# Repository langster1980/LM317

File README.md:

LM317
=====

Released by Alexander Lang under the creative commons share alike licence - 01-09-2012

Eagle design files for the LM317 Variable power supply.

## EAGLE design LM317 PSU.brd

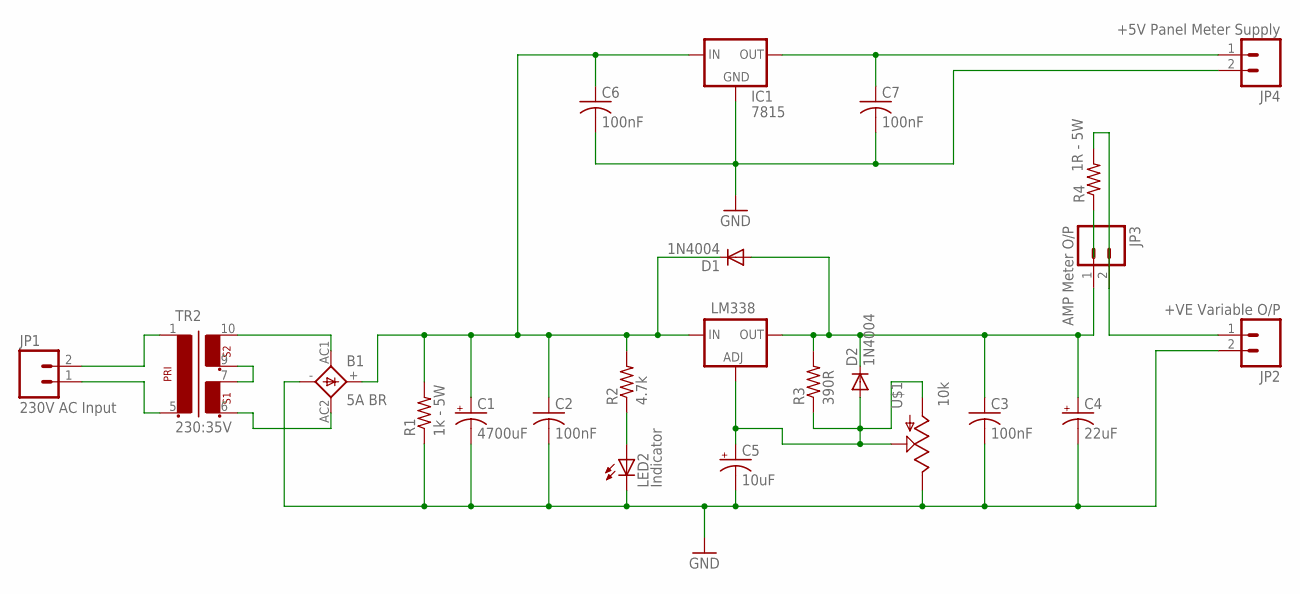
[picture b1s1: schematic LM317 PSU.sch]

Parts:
B1: 5A BR; GBPC80X
C1: 4700uF; E7,5-16
C2, C3, C6, C7: 100nF; C025-040X050
C4: 22uF; E5-6
C5: 10uF; E5-6
D1, D2: 1N4004; DO41-10
IC1: 7815; TO220-IGO
JP1: 230V AC Input; SCREWTERMINAL-5MM-2
JP2: +VE Variable O/P; SCREWTERMINAL-5MM-2
JP3: AMP Meter O/P; SCREWTERMINAL-5MM-2
JP4: +5V Panel Meter Supply; SCREWTERMINAL-5MM-2
LED2: Indicator; LED5MM
LM338: V_REG_317SINK; TO220-ADJ
R1: 1k - 5W; V234/12
R2: 4.7k; 0805-THM
R3: 390R; 0805-THM
R4: 1R - 5W; V234/12
TR2: 230:35V; EI42-2
U$1: 10k; POT_ALPHA_RV16AF-20

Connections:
GND: B1.-, C1.-, C2.2, C3.2, C4.-, C5.-, C6.2, C7.2, IC1.GND, JP2.2, JP4.2, LED2.K (C), R1.1, U$1.3 (E)
unnamed: JP1.2, TR2.1
unnamed: JP1.1, TR2.5 (2)
unnamed: B1.AC1, TR2.10 (6)
unnamed: B1.AC2, TR2.6 (3)
unnamed: TR2.7 (4), TR2.9 (5)
unnamed: B1.+, C1.+, C2.1, C6.1, D1.C, IC1.IN, LM338.IN, R1.2, R2.2
unnamed: LED2.A, R2.1
unnamed: C5.+, D2.A, LM338.ADJ, R3.1, U$1.1 (A), U$1.2 (S)
unnamed: C7.1, IC1.OUT, JP4.1
unnamed: C3.1, C4.+, D1.A, D2.C, JP3.1, LM338.OUT, R3.2
unnamed: JP2.1, JP3.2, R4.2

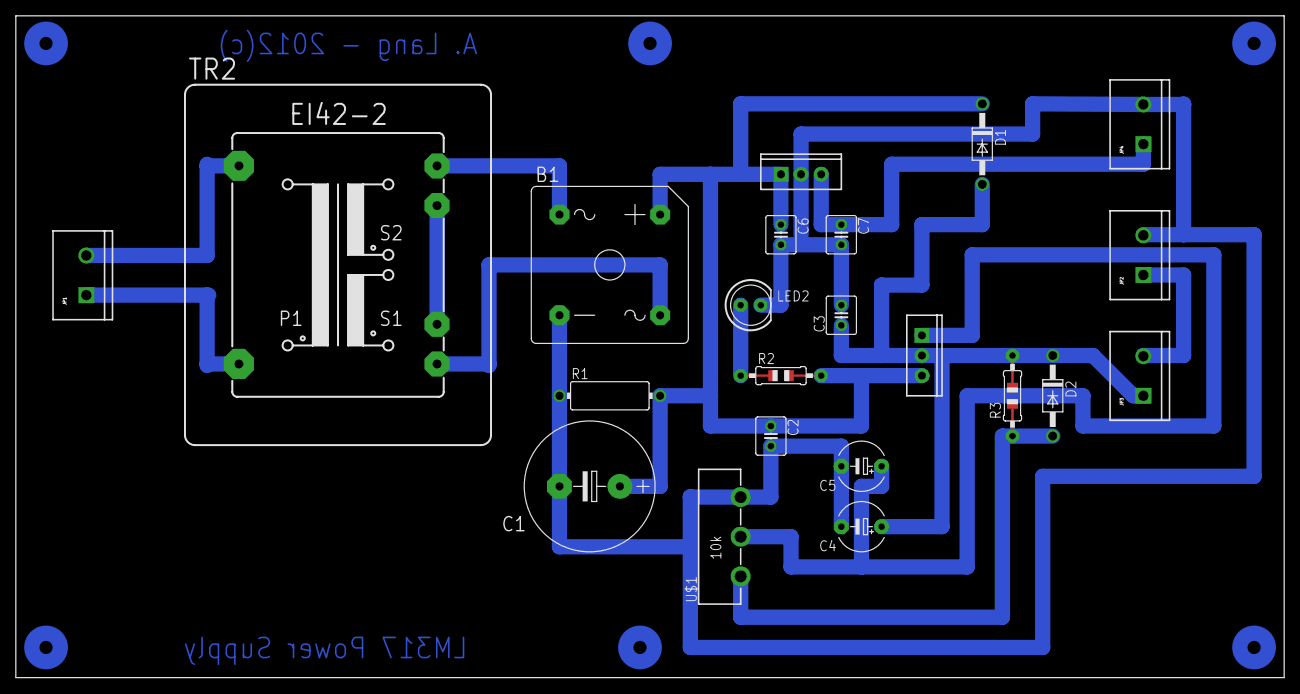
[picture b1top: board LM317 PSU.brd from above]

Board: 2 copper layers, 160.0 x 83.5 mm, 22 parts (0 on the bottom side), 12 nets.

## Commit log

2012-09-28 Uploaded eagle design files for LM317 power supply
2012-09-28 Updated Eagle files after mistake noticed

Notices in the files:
parts and their libraries:
SparkFun: Licensing: CC v3.0 Share-Alike You are welcome to use this library for commercial purposes.
